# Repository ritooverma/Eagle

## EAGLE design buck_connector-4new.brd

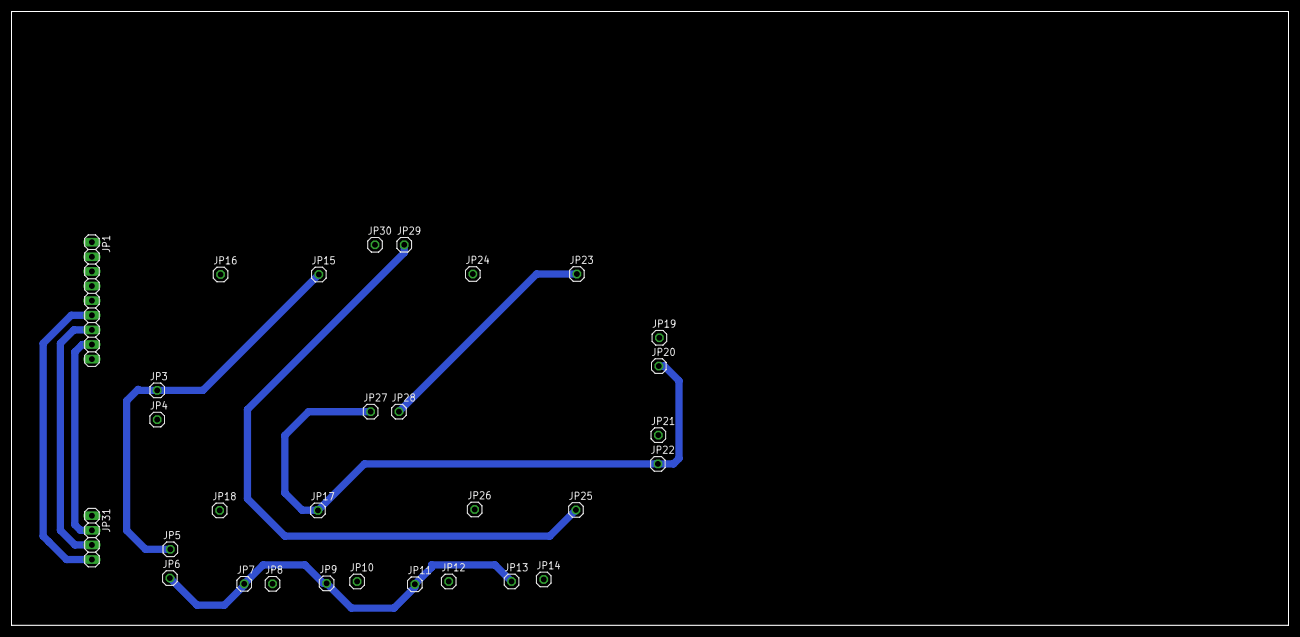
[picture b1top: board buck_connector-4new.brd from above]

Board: 2 copper layers, 221.9 x 106.7 mm, 30 parts (0 on the bottom side), 9 nets.

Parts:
JP1: 1X09
JP3, JP4, JP5, JP6, JP7, JP8, JP9, JP10, JP11, JP12, JP13, JP14, JP15, JP16, JP17, JP18, JP19, JP20, JP21, JP22, JP23, JP24, JP25, JP26, JP27, JP28, JP29, JP30: 1X01
JP31: 1X04

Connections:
GND: JP1.9, JP4.1, JP8.1, JP10.1, JP12.1, JP14.1, JP16.1, JP18.1, JP19.1, JP21.1, JP24.1, JP26.1, JP30.1, JP31.1
unnamed: JP6.1, JP7.1, JP9.1, JP11.1, JP13.1
unnamed: JP1.8, JP31.2
unnamed: JP1.7, JP31.3
unnamed: JP1.6, JP31.4
unnamed: JP3.1, JP5.1, JP15.1
unnamed: JP17.1, JP20.1, JP22.1, JP27.1
unnamed: JP23.1, JP28.1
unnamed: JP25.1, JP29.1
